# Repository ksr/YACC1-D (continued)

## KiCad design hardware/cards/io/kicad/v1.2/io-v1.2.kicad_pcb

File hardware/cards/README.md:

# hardware/cards

One folder per card: README.md, kicad/ (current), eagle/<rev>/ (deprecated), docs/, bom/.

_Contents migrated 2026-09-19; MIGRATION.md at the repo root says which copy each item came from._

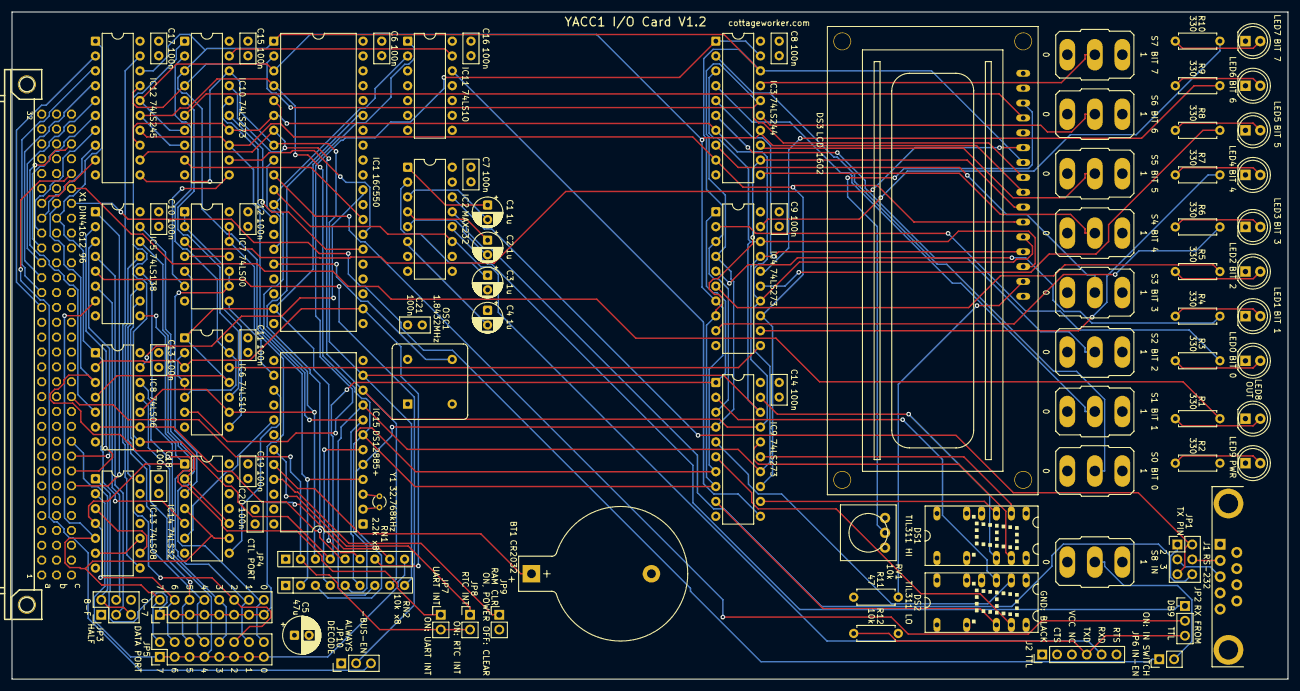
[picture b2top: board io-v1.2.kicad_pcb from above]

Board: 4 copper layers, 218.0 x 114.0 mm, 89 parts (0 on the bottom side), 129 nets.

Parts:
BT1: CR2032; BatteryHolder_Keystone_103_1x20mm
C1, C2, C3, C4: 1u; CP_Radial_D5.0mm_P2.50mm
C5: 47u 16V; CP_Radial_D6.3mm_P2.50mm
C6, C7, C8, C9, C10, C11, C12, C13, C14, C15, C16, C17, C18, C19, C20, C21: 100n; C_Disc_D5.0mm_W2.5mm_P2.50mm
DS1: TIL311 HI; HTIL311A
DS2: TIL311 LO; HTIL311A
DS3: LCD 1602; LCD1602
IC1: 16C550; DIP-40_W15.24mm
IC2: MAX232; DIP-16_W7.62mm
IC3: 74LS244; DIP-20_W7.62mm
IC4, IC9, IC10: 74LS273; DIP-20_W7.62mm
IC5: 74LS138; DIP-16_W7.62mm
IC6, IC11: 74LS10; DIP-14_W7.62mm
IC7: 74LS00; DIP-14_W7.62mm
IC8: 74LS06; DIP-14_W7.62mm
IC12: 74LS245; DIP-20_W7.62mm
IC13: 74LS08; DIP-14_W7.62mm
IC14: 74LS32; DIP-14_W7.62mm
IC15: DS12885+; DIP-24_W15.24mm
J1: RS-232; DSUB-9_Socket_Horizontal_IO-V1.1
J2: TTL SERIAL; PinHeader_1x06_P2.54mm_Vertical
JP1: TX PIN; PinHeader_2x03_P2.54mm_Vertical
JP2: RX FROM; PinHeader_1x03_P2.54mm_Vertical
JP3: HALF; PinHeader_2x03_P2.54mm_Vertical
JP4: CTL PORT; PinHeader_2x08_P2.54mm_Vertical
JP5: DATA PORT; PinHeader_2x08_P2.54mm_Vertical
JP6: IN-EN; PinHeader_1x02_P2.54mm_Vertical
JP7: UART INT; PinHeader_1x02_P2.54mm_Vertical
JP8: RTC INT; PinHeader_1x02_P2.54mm_Vertical
JP9: RAM CLR; PinHeader_1x02_P2.54mm_Vertical
JP10: DECODE; PinHeader_1x03_P2.54mm_Vertical
LED0: 0; LED_D5.0mm
LED1: 1; LED_D5.0mm
LED2: 2; LED_D5.0mm
LED3: 3; LED_D5.0mm
LED4: 4; LED_D5.0mm
LED5: 5; LED_D5.0mm
LED6: 6; LED_D5.0mm
LED7: 7; LED_D5.0mm
LED8: OUT; LED_D5.0mm
LED9: PWR; LED_D5.0mm
OSC1: 1.8432MHz; Oscillator_DIP-8
R1, R2, R3, R4, R5, R6, R7, R8, R9, R10: 330; R_Axial_DIN0207_L6.3mm_D2.5mm_P7.62mm_Horizontal
R11: 47; R_Axial_DIN0207_L6.3mm_D2.5mm_P7.62mm_Horizontal
R12: 10k; R_Axial_DIN0207_L6.3mm_D2.5mm_P7.62mm_Horizontal
RN1: 2.2k x8; R_Array_SIP9
RN2: 10k x8; R_Array_SIP9
RV1: 10k; Potentiometer_Trim_3386_Inline
S0: 0; SW_Toggle_M9040P
S1: 1; SW_Toggle_M9040P
S2: 2; SW_Toggle_M9040P
S3: 3; SW_Toggle_M9040P
S4: 4; SW_Toggle_M9040P
S5: 5; SW_Toggle_M9040P
S6: 6; SW_Toggle_M9040P
S7: 7; SW_Toggle_M9040P
S8: IN; SW_Toggle_M9040P
X1: DIN41612 96; FABC96R
Y1: 32.768kHz; Crystal_C26-LF_D2.1mm_L6.5mm_Vertical

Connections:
/-B-RESET: IC4.1, IC8.8, IC9.1, IC10.1, RN1.4
/-BUS-EN: JP10.3, X1.C28
/-INT: JP7.2, JP8.2, RN1.2, X1.C13
/-IO-ADDRSEL: IC7.12, IC7.13, IC13.1, JP4.1, JP4.3, JP4.5, JP4.7, JP4.9, JP4.11, JP4.13, JP4.15, RN1.8
/-IO-DATASEL: IC8.11, IC13.2, JP5.1, JP5.3, JP5.5, JP5.7, JP5.9, JP5.11, JP5.13, JP5.15, RN1.9
/-IO-RD: IC8.1, IC12.1, IC14.5, X1.B25
/-IO-SEL0: IC5.15, JP4.16, JP5.16
/-IO-SEL1: IC5.14, JP4.14, JP5.14
/-IO-SEL2: IC5.13, JP4.12, JP5.12
/-IO-SEL3: IC5.12, JP4.10, JP5.10
/-IO-SEL4: IC5.11, JP4.8, JP5.8
/-IO-SEL5: IC5.10, JP4.6, JP5.6
/-IO-SEL6: IC5.9, IC13.4, IC14.1, JP4.4, JP5.4
/-IO-SEL7: IC5.7, IC13.5, IC14.4, IC14.9, JP4.2, JP5.2
/-IO-WR: IC8.3, IC14.2, IC14.10, X1.B26
/-RESET: IC8.5, X1.C30
/AS#: IC7.9, IC7.10, IC14.3
/BUFEN#: IC12.19, IC13.8
/C1+: C1.1, IC2.1
/C1-: C1.2, IC2.3
/C2+: C2.1, IC2.4
/C2-: C2.2, IC2.5
/CTLCK: IC7.6, IC10.11
/DATA0: IC12.2, X1.A19
/DATA1: IC12.3, X1.A20
/DATA2: IC12.4, X1.A21
/DATA3: IC12.5, X1.A22
/DATA4: IC12.6, X1.A23
/DATA5: IC12.7, X1.A24
/DATA6: IC12.8, X1.A25
/DATA7: IC12.9, X1.A26
/DB9-2: J1.2, JP1.4
/DB9-3: J1.3, JP1.3
/G2B#: IC5.5, JP10.2
/HALF-G1: IC5.6, JP3.4
/HALF-G2A: IC5.4, JP3.3
/ICLK: IC1.9, IC1.15
/ID0: DS3.7, IC1.1, IC3.18, IC4.3, IC9.3, IC10.3, IC12.18, IC15.4, RN2.2
/ID1: DS3.8, IC1.2, IC3.16, IC4.4, IC9.4, IC10.4, IC12.17, IC15.5, RN2.3
/ID2: DS3.9, IC1.3, IC3.14, IC4.7, IC9.7, IC10.7, IC12.16, IC15.6, RN2.4
/ID3: DS3.10, IC1.4, IC3.12, IC4.8, IC9.8, IC10.8, IC12.15, IC15.7, RN2.5
/ID4: DS3.11, IC1.5, IC3.9, IC4.13, IC9.13, IC10.13, IC12.14, IC15.8, RN2.6
/ID5: DS3.12, IC1.6, IC3.7, IC4.14, IC9.14, IC10.14, IC12.13, IC15.9, RN2.7
/ID6: DS3.13, IC1.7, IC3.5, IC4.17, IC9.17, IC10.17, IC12.12, IC15.10, RN2.8
/ID7: DS3.14, IC1.8, IC3.3, IC4.18, IC9.18, IC10.18, IC12.11, IC15.11, RN2.9
/IN: JP6.1, X1.C26
/INSW: JP6.2, S8.2
/IO-ADDR0: IC5.1, X1.C7
/IO-ADDR1: IC5.2, X1.C8
/IO-ADDR2: IC5.3, X1.C9
/IO-ADDR3: JP3.2, JP3.5, X1.C10
/IO-ADDRSEL: IC7.4, IC7.11
/IO-RD: IC1.22, IC6.3, IC8.2, RN1.7
/IO-SELDATA: IC1.12, IC6.2, IC6.4, IC6.9, IC8.10, IC11.2, RN1.3
/IO-WR: IC1.19, IC6.1, IC6.11, IC7.5, IC8.4, IC11.1, RN1.6
/LCD-BL: DS3.15, R11.2
/LCD-E: DS3.6, IC7.3
/LCD-ENABLE: IC6.10, IC10.5
/LCD-REGISTER: DS3.4, IC10.6
/LCD-VO: DS3.3, RV1.2
/LCDSTB#: IC6.8, IC7.1, IC7.2
/LEDA0: LED0.2, R3.1
/LEDA1: LED1.2, R4.1
/LEDA2: LED2.2, R5.1
/LEDA3: LED3.2, R6.1
/LEDA4: LED4.2, R7.1
/LEDA5: LED5.2, R8.1
/LEDA6: LED6.2, R9.1
/LEDA7: LED7.2, R10.1
/LEDCK: IC4.11, IC6.12
/LQ0: IC4.2, R3.2
/LQ1: IC4.5, R4.2
/LQ2: IC4.6, R5.2
/LQ3: IC4.9, R6.2
/LQ4: IC4.12, R7.2
/LQ5: IC4.15, R8.2
/LQ6: IC4.16, R9.2
/LQ7: IC4.19, R10.2
/OUT: R1.2, X1.C27
/OUTA: LED8.2, R1.1
/PWRA: LED9.2, R2.1
/RCLR#: IC15.21, JP9.1
/RESET: IC1.35, IC8.6, IC8.9, RN1.5
/RTC-AS: IC7.8, IC15.14
/RTC-IRQ#: IC15.19, JP8.1
/RTC-RD#: IC14.6, IC15.17
/RTC-WR#: IC14.8, IC15.15
/RTC-X1: IC15.2, Y1.1
/RTC-X2: IC15.3, Y1.2
/RX: IC1.10, JP2.2
/RX-232: IC2.12, JP2.1
/RX-IN: IC2.13, JP1.1, JP1.6
/RX-TTL: J2.4, JP2.3, R12.1
/SELPORT#: IC13.3, IC13.9
/SELRTC#: IC13.6, IC13.10
/SW0: IC3.2, S0.2
/SW1: IC3.4, S1.2
/SW2: IC3.6, S2.2
/SW3: IC3.8, S3.2
/SW4: IC3.11, S4.2
/SW5: IC3.13, S5.2
/SW6: IC3.15, S6.2
/SW7: IC3.17, S7.2
/SWITCH-LED: IC6.5, IC6.13, IC10.2
/SWOE#: IC3.1, IC3.19, IC6.6
/TH0: DS1.3, IC9.12
/TH1: DS1.2, IC9.15
/TH2: DS1.13, IC9.16
/TH3: DS1.12, IC9.19
/TIL311: IC10.19, IC11.13
/TILCK: IC9.11, IC11.12
/TL0: DS2.3, IC9.2
/TL1: DS2.2, IC9.5
/TL2: DS2.13, IC9.6
/TL3: DS2.12, IC9.9
/TX: IC1.11, IC2.11, J2.5
/TX-OUT: IC2.14, JP1.2, JP1.5
/UART-A0: IC1.28, IC10.9
/UART-A1: IC1.27, IC10.12
/UART-A2: IC1.26, IC10.15
/UART-CS: IC1.13, IC10.16
/UART-INT: IC1.30, IC8.13
/UCLK: IC1.16, OSC1.5
/UINT#: IC8.12, JP7.1
/V+: C3.1, IC2.2
/V-: C4.2, IC2.6
/VBAT: BT1.1, IC15.20
GND: BT1.2, C4.1, C5.2, C6.2, C7.2, C8.2, C9.2, C10.2, C11.2, C12.2, C13.2, C14.2, C15.2, C16.2, C17.2, C18.2, C19.2, C20.2, C21.2, DS1.5, DS1.7, DS1.8, DS2.5, DS2.7, DS2.8, DS3.1, DS3.5, DS3.16, IC1.14, IC1.20, IC1.25, IC2.8, IC2.15, IC3.10, IC4.10, IC5.8, IC6.7, IC7.7, IC8.7, IC9.10, IC10.10, IC11.3, IC11.4, IC11.5, IC11.7, IC11.9, IC11.10, IC11.11, IC12.10, IC13.7, IC13.12, IC13.13, IC14.7, IC14.12, IC14.13, IC15.1, IC15.12, IC15.13, IC15.16, J1.5, J1.SH, J2.1, J2.2, JP3.1, JP9.2, JP10.1, LED0.1, LED1.1, LED2.1, LED3.1, LED4.1, LED5.1, LED6.1, LED7.1, LED8.1, LED9.1, OSC1.4, RV1.3, S0.3, S1.3, S2.3, S3.3, S4.3, S5.3, S6.3, S7.3, S8.3, X1.A1, X1.A32, X1.B1, X1.B32, X1.C1, X1.C32
VCC: C3.2, C5.1, C6.1, C7.1, C8.1, C9.1, C10.1, C11.1, C12.1, C13.1, C14.1, C15.1, C16.1, C17.1, C18.1, C19.1, C20.1, C21.1, DS1.1, DS1.14, DS2.1, DS2.14, DS3.2, IC1.18, IC1.21, IC1.36, IC1.37, IC1.38, IC1.39, IC1.40, IC2.10, IC2.16, IC3.20, IC4.20, IC5.16, IC6.14, IC7.14, IC8.14, IC9.20, IC10.20, IC11.14, IC12.20, IC13.14, IC14.14, IC15.18, IC15.24, JP3.6, OSC1.1, OSC1.8, R2.2, R11.1, R12.2, RN1.1, RN2.1, RV1.1, S0.1, S1.1, S2.1, S3.1, S4.1, S5.1, S6.1, S7.1, S8.1, X1.A2, X1.A31, X1.B2, X1.B31, X1.C2, X1.C31

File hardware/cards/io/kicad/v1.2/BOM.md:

# I/O card V1.2 - bill of materials

GENERATED by `gen_io12.py bom` from `io12_netlist.py` (2026-11-18) - do not edit. 89 parts. Buy every IC in a socket (the UART, the clock chip and the TIL311s at least): 6 x 14-pin 7.62 mm, 2 x 16-pin 7.62 mm, 5 x 20-pin 7.62 mm, 1 x 24-pin 15.24 mm, 1 x 40-pin 15.24 mm; a 4-pin socket for the oscillator, two 14-pin sockets for the TIL311s and a 16-way socket strip for the LCD.

| Qty | Value | Footprint | References | Buy / note |
|---|---|---|---|---|
| 1 | CR2032 | BatteryHolder_Keystone_103_1x20mm | BT1 | Keystone 103, a flat holder for one CR2032 (an upright holder is taller than the room between cards) |
| 4 | 1u | CP_Radial_D5.0mm_P2.50mm | C1, C2, C3, C4 |  |
| 1 | 47u 16V | CP_Radial_D6.3mm_P2.50mm | C5 | bulk |
| 16 | 100n | C_Disc_D5.0mm_W2.5mm_P2.50mm | C6, C7, C8, C9, C10, C11, C12, C13, C14, C15, C16, C17, C18, C19, C20, C21 |  |
| 1 | TIL311 HI | HTIL311A | DS1 | TIL311 (or HP 5082-7340: same pins), in a socket |
| 1 | TIL311 LO | HTIL311A | DS2 | TIL311 (or HP 5082-7340), in a socket |
| 1 | LCD 1602 | LCD1602 | DS3 | HD44780 16 x 2 module, 80 x 36 mm, a 16-pin row along its upper edge (pin 1 at the left), on a 16-way socket strip and four 2.5 mm standoffs |
| 1 | 16C550 | DIP-40_W15.24mm | IC1 | a 16550 in DIP-40: Exar XR16C550CP (the V1.1 card's), TI TL16C550CN or PC16550DN |
| 1 | MAX232 | DIP-16_W7.62mm | IC2 | MAX232 with 1 uF capacitors (a MAX232A or MAX202 runs on them too) |
| 1 | 74LS244 | DIP-20_W7.62mm | IC3 | switch buffer: S0-S7 to ID0-7 (IN P1 with SWITCH-LED) |
| 3 | 74LS273 | DIP-20_W7.62mm | IC4, IC9, IC10 |  |
| 1 | 74LS138 | DIP-16_W7.62mm | IC5 | port decode: -IO-SEL0..7, the eight ports of the card's half (JP3) |
| 2 | 74LS10 | DIP-14_W7.62mm | IC6, IC11 |  |
| 1 | 74LS00 | DIP-14_W7.62mm | IC7 | the LCD's E; the control latch's clock; the clock chip's AS; IO-ADDRSEL |
| 1 | 74LS06 | DIP-14_W7.62mm | IC8 | open collector: IO-RD, IO-WR, RESET, -B-RESET, IO-SELDATA, the UART's -INT |
| 1 | 74LS245 | DIP-20_W7.62mm | IC12 | data buffer: the bus's DATA0-7 to the card's ID0-7, direction from -IO-RD |
| 1 | 74LS08 | DIP-14_W7.62mm | IC13 | the buffer's enable: one of the card's four ports addressed; one gate spare |
| 1 | 74LS32 | DIP-14_W7.62mm | IC14 | the clock chip's strobes from the bus's -IO-RD and -IO-WR; one gate spare |
| 1 | DS12885+ | DIP-24_W15.24mm | IC15 | DS12885+ (Analog Devices / Maxim), the 24-pin PDIP: not the DS12887 module (its pins 2, 3, 20 are not connected) |
| 1 | RS-232 | DSUB-9_Socket_Horizontal_IO-V1.1 | J1 | 9-way D socket (female), right angle, as the V1.1 card's: pin rows 2.84 mm apart, 10.2 mm behind the board's edge, mounting holes 25.0 mm apart |
| 1 | TTL SERIAL | PinHeader_1x06_P2.54mm_Vertical | J2 | 6-pin header, 2.54 mm: an FTDI TTL-232R-5V cable's socket, its black wire (GND) on pin 1 |
| 1 | TX PIN | PinHeader_2x03_P2.54mm_Vertical | JP1 | the null-modem block. 1-3 and 2-4: the card sends on DB9 pin 2; 3-5 and 4-6: on pin 3 |
| 1 | RX FROM | PinHeader_1x03_P2.54mm_Vertical | JP2 | 1-2: the UART hears the DB9; 2-3: the TTL header |
| 1 | HALF | PinHeader_2x03_P2.54mm_Vertical | JP3 | 3-5 and 4-6: ports P0-P7; 1-3 and 2-4: P8-PF |
| 1 | CTL PORT | PinHeader_2x08_P2.54mm_Vertical | JP4 | one jumper: the control port. 15-16 = port 0 ... 1-2 = port 7 |
| 1 | DATA PORT | PinHeader_2x08_P2.54mm_Vertical | JP5 | one jumper: the data port. 13-14 = port 1 |
| 1 | IN-EN | PinHeader_1x02_P2.54mm_Vertical | JP6 | fitted: the IN switch drives the bus line IN |
| 1 | UART INT | PinHeader_1x02_P2.54mm_Vertical | JP7 | fitted: the UART's INT drives -INT |
| 1 | RTC INT | PinHeader_1x02_P2.54mm_Vertical | JP8 | fitted: the clock's -IRQ drives -INT |
| 1 | RAM CLR | PinHeader_1x02_P2.54mm_Vertical | JP9 | fitted with the power off: the clock chip's RAM is cleared |
| 1 | DECODE | PinHeader_1x03_P2.54mm_Vertical | JP10 | 1-2: the ports are decoded always, as on V1.1 (the bus tester can drive the card); 2-3: only while -BUS-EN is low |
| 1 | 0 | LED_D5.0mm | LED0 | LED bit 0 |
| 1 | 1 | LED_D5.0mm | LED1 | LED bit 1 |
| 1 | 2 | LED_D5.0mm | LED2 | LED bit 2 |
| 1 | 3 | LED_D5.0mm | LED3 | LED bit 3 |
| 1 | 4 | LED_D5.0mm | LED4 | LED bit 4 |
| 1 | 5 | LED_D5.0mm | LED5 | LED bit 5 |
| 1 | 6 | LED_D5.0mm | LED6 | LED bit 6 |
| 1 | 7 | LED_D5.0mm | LED7 | LED bit 7 |
| 1 | OUT | LED_D5.0mm | LED8 | the bus line OUT (ON / OFF) |
| 1 | PWR | LED_D5.0mm | LED9 | 5 mm LED |
| 1 | 1.8432MHz | Oscillator_DIP-8 | OSC1 | 1.8432 MHz oscillator, 5 V, half-size (8-pin DIP) can, as the V1.1 card's (ECS-2100AX): the monitor's divisor 3 gives 38400 baud. Its pin 1 is tied to +5 V on the board: not connected in the can, or an enable that is on when high |
| 10 | 330 | R_Axial_DIN0207_L6.3mm_D2.5mm_P7.62mm_Horizontal | R1, R2, R3, R4, R5, R6, R7, R8, R9, R10 |  |
| 1 | 47 | R_Axial_DIN0207_L6.3mm_D2.5mm_P7.62mm_Horizontal | R11 | 47 ohm for a module with no resistor of its own for its backlight; a wire link if the module has one |
| 1 | 10k | R_Axial_DIN0207_L6.3mm_D2.5mm_P7.62mm_Horizontal | R12 | the TTL header's line into the UART held high with no cable |
| 1 | 2.2k x8 | R_Array_SIP9 | RN1 | pull-ups: the open-collector strobes, -INT, the two port selects |
| 1 | 10k x8 | R_Array_SIP9 | RN2 | ID0-7 pull-ups (the buffer off) |
| 1 | 10k | Potentiometer_Trim_3386_Inline | RV1 | 10k trimmer, Bourns 3386 with its three pins in a row |
| 1 | 0 | SW_Toggle_M9040P | S0 | M9040P toggle (on-on, PCB pins), as the V1.1 card's |
| 1 | 1 | SW_Toggle_M9040P | S1 | M9040P toggle (on-on, PCB pins), as the V1.1 card's |
| 1 | 2 | SW_Toggle_M9040P | S2 | M9040P toggle (on-on, PCB pins), as the V1.1 card's |
| 1 | 3 | SW_Toggle_M9040P | S3 | M9040P toggle (on-on, PCB pins), as the V1.1 card's |
| 1 | 4 | SW_Toggle_M9040P | S4 | M9040P toggle (on-on, PCB pins), as the V1.1 card's |
| 1 | 5 | SW_Toggle_M9040P | S5 | M9040P toggle (on-on, PCB pins), as the V1.1 card's |
| 1 | 6 | SW_Toggle_M9040P | S6 | M9040P toggle (on-on, PCB pins), as the V1.1 card's |
| 1 | 7 | SW_Toggle_M9040P | S7 | M9040P toggle (on-on, PCB pins), as the V1.1 card's |
| 1 | IN | SW_Toggle_M9040P | S8 | M9040P toggle (on-on, PCB pins), as the V1.1 card's |
| 1 | DIN41612 96 | FABC96R | X1 | bus connector (blank V3.2 card) |
| 1 | 32.768kHz | Crystal_C26-LF_D2.1mm_L6.5mm_Vertical | Y1 | 32.768 kHz watch crystal for a 6 pF load (the DS12885 has the load capacitors inside): a 12.5 pF crystal runs fast |

Shunts: one each for JP4 and JP5 (the two ports), JP2 and JP10 (on 1-2, as V1.1, unless the decoder is to follow -BUS-EN), two each for JP3 and JP1, one for JP6 (IN); JP7, JP8 and JP9 are left open.

The 74LS types are the V1.1 card's. The three latches may be 74HCT273 (the LEDs are a little brighter); the buffer IC12 stays a 74LS245 or 74HCT245 (TTL input levels on both sides).

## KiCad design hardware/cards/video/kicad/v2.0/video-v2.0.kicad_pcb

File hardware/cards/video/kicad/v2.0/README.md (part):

# video-v2.0 — KiCad design master for the video card

**This card will not be built (decided 2026-11-17): the video card to build is the V4 (`../v4.0`,
`docs/cards/video-v4.md`). Nothing here was ordered. The design is kept as it stood, unchanged, for reference; do
not order from this folder.**

**The master since 2026-10-22. Ready to order since 2026-10-23 (re-reviewed, every re-review finding applied); not
ordered. Revised 2026-10-26 before the order: the DB9's VSYNC polarity jumper JP4** (below), the board routed again
2026-10-27, with the board-layout rules' silkscreen and cottageworker.com on it; the gerbers exported again
2026-11-03 with every part's value on the silk (silk only) and, the same day, with each power plane in one piece
(16 power pads connected solid, inner layers only: "Planes (2026-11-03)"; `video-v2.0-gerbers.zip`, what to upload:
"Ordering" below). V2.0 is the v1.3 card (`../v1.3/`: 6845, IDT7134 text RAM,
the DOTS jumper, 12 MHz, both fonts in one character generator) plus a **graphics layer**, **every register on I/O ports
PA-PE** and **two PS/2 ports** on an ATmega328P with an **INT jumper**. The design note is `BACKLOG.md` "Video card
V2.0"; the theory `docs/cards/video-v2.md`; the ATmega's firmware `embedded/video-ps2`; the picture and the CPU
side `tools/vidsim.py --card v2.0`.

**Revised 2026-10-22 after the design review** (`hardware/cards/video/reviews/v2.0.md`, its status table at the top):
every HIGH and MEDIUM finding is in the circuit or the firmware, and two features were added - **direct mode** (with
GFX-ON = 0 the CPU owns the graphics RAM: a plain SRAM at any clock the machine runs) and the **text-only build** (the
graphics chips left off, a status bit saying so). **Re-reviewed 2026-10-23** (`hardware/cards/video/reviews/v2.0-r2.md`,
HIGH 0, MED 1, LOW 9, INFO 6; its status table at the top): the MD-60SM side-leg slots widened (R2-1), IC55's socket
clear of its neighbours (R2-2), the bus -RESET buffered (R2-3), the BOM, the README's statements, the silkscreen, the
timing test and the firmware; the rest are driver rules and bench measurements.

Unlike v1.x (Eagle conversions edited in KiCad) this design is **generated**: `v20_netlist.py` is the circuit,
`gen_v20.py` draws the schematic (since 2026-10-24 a root sheet and eight functional sheets with the nets drawn as
wires: "The schematic" below), builds the board and writes `BOM.md`; `build.sh` routes and checks it. Change the circuit in
`v20_netlist.py`, the placement in `gen_v20.py` (`PLACE`), then run `./build.sh` (KiCad 10, Freerouting 1.9 in `FRJAR`,
default `~/freerouting/freerouting.jar`, which opens a window while it runs; `SEEDS="..."` and `MP=` choose the
component orders and passes). `tools/eagle_to_kicad_all.py` never writes here (`MASTER` marker).

## The board

- **218.42 x 113.97 mm** (x 17.747-236.167): the blank V3.2 card's outline lengthened to the sequencer logic V2.1l's
  218 mm, so it needs the same slot space; X1 (DIN 41612) exactly where every card has it, copper keepouts round its
  two screws.
- **4 layers**, the v1.3 / memory card v2.0 stack-up and rules: In1.Cu a solid GND plane, In2.Cu a solid VCC plane, GND
  and VCC never routed (every power pin is a through-hole pad on its plane); signals 0.25 mm, clearance 0.2 mm, vias
  0.8 / 0.4 mm.
- **Placement** (`gen_v20.py` `PLACE`; pin 1 of every DIP at the top left, each 100 nF beside its IC's VCC pin):
  row A (top) the port decode, strobes, the inverters IC46 (beside the control register they mostly serve), the control
  register, status buffers, the PS/2 and graphics latches, WRQ and the video driver IC27; on the left the 600-mil parts (IC15 text RAM, IC17 6845, IC39 62256, IC25 28C64) and IC18 with SV3 /
  RN2; row B the graphics address muxes, display latch and shifter, the ATmega, with the GD pull-ups RN3 standing between
  IC38 and IC42; under IC42 / IC43, on its side, the direct-mode read buffer IC55 (the band under the muxes is left to
  the routing); row C the text pipeline and the gates, with the text-only pads R25 / R26 in the gaps beside IC1; row D
  the clock chain (IC28, IC21, IC20 with Q2, SV4), the remaining gates (IC32 among them, beside the counter whose QC and
  RCO it ORs) and IC54 (turned round, beside J4); the right
  edge DB9 (X2) with its VSYNC polarity jumper JP4 standing beside it (2026-10-26), RCA (J1), the keyboard (J2) and mouse (J3) Mini-DINs with their faces at the board edge, F1, the FTDI header J4 (a legend
  at every pin), the PWR LED. `gen_v20.py place` checks that no two courtyards overlap and, since the re-review (R2-2),
  that every DIP **socket** fits: each socket's outline (the pin rows + 1.3 mm at the sides, the end pins + 1.9 mm at
  the ends: the widest stamped sockets) clear of every other socket and of every other part's pads and body. The
  closest are IC55 (on its side between IC42 above and IC19 / IC1 below) with 0.02 mm to IC42's and 0.10 to IC19's /
  IC1's, IC55 / C59 0.17, IC49 / R12 0.17, IC25 / IC39 0.18 mm; with turned-pin sockets (1.27 mm end walls) IC55 has
  ~0.65 mm. RN3 and C59 stand 0.3 mm left of the middle of their gap for it.
- **Silkscreen** (R2-9; the board-layout rules since 2026-10-24, below): `gen_v20.py silk` writes every legend afresh
  and places it and every reference clear of the other silk, the pads, the edge and every part's body, its own
  included (`silk_texts()`, `silk_place()`). Each IC's type stands on the reference's line ("IC30 74LS138"); the
  jumpers and the LED carry their function and the jumpers each position's meaning. The jack legends "KEYBOARD (PURPLE)" and
  "MOUSE (GREEN)" stand turned beside each jack's body; the Mini-DIN outline is broken round its side-leg pads and stops
  short of the board edge. The card's name stands in the band under the graphics muxes. Since 2026-11-03 every
  resistor, network, capacitor, crystal and the fuse carries its value beside its reference ("R10 1k", "RN3 10k x8",
  "C16 47u", "Y1 16MHz", "F1 0.5A").

## The board-layout rules (2026-10-24)

The rules for every YACC1 board (switches, buttons, LEDs and outside-cable connectors on the front edge, the edge
farthest from the bus connector; every reference readable with the parts fitted, never under a chip, socket or module,
an IC's type beside it; every switch, button and LED labelled with its function, each position of a switch with what
it selects) came after this board was routed and before it was ordered. V2.0 took them on the **silkscreen only**
(2026-10-24): no part moved, the copper and the drills stayed the route of 2026-10-23 (`ed7c060`, order 5, 285 vias).
The VSYNC jumper JP4 (2026-10-26) follows them too: a jumper block near the front edge, its positions labelled. The
board was routed afresh for it ("Results"). Every part's value beside its reference (2026-11-03) came the same way,
on the silkscreen only ("Part values" below).

| Rule | On this board |
|---|---|
| front edge | the DB9 X2, the RCA J1, the PS/2 jacks J2 / J3 and the PWR LED stand at the right-hand edge, opposite X1; the DB9's VSYNC jumper JP4 stands beside the DB9. The FTDI header J4 (the ATmega's programming port) stays where it is, 24 mm in from that edge, with its pin legend: moving it would mean a new route |
| IC type beside the reference | all 40 ICs, on one line with the reference ("IC30 74LS138"): the value of each as the parts list has it, the grade included - IC17 **HD68B45SP / MC68B45P**, IC25 **AT28C64B-15**, IC49 **ATmega328P-P** (2026-11-10; "6845", "28C64" and "ATmega328P" before). Above the IC where there is room, else below it, else turned in the gap beside it (IC19, IC28, IC49 on the left, IC53 on the right); IC49's, too long for its gap on one line, stands there on two ("Labels" below) |
| no reference under a part | every text is kept off every part's body, its own included (its ink off the bodies below, and since 2026-11-10 its whole text box off every part's Fab outline, as `pcb-check` measures it): a DIP's body is the outline of the widest stamped socket (`socket_check`: the pin rows + 1.3 mm, the end pins + 1.9 mm), X1's the DIN 41612 housing (its silk, pads and 2.5 mm past its ends), J1's its outline and pads. R10, R25, R26 and R27 had their references inside their own outline: they now stand beside it. X1's reference left the housing's end (at the top-left corner, x 18.9, y 16.1, until 2026-11-10; now beside the housing with its type, "X1 DIN41612 96"); J1's, hidden by the RCA library footprint, is shown left of the jack. Checked by the texts' ink against every body and socket outline: before, 37 references stood on one - 26 capacitors' on a neighbouring IC's socket wall, IC1's on IC55's socket, IC19's, IC25's and IC54's on their own socket, J2's on J1, R15's and RN3's on IC25's / IC38's socket, R10's, R25's, R26's and R27's on their own body; now none |
| functions and positions | **LED1 PWR**. **JP2 DOTS**, "ON=8 OFF=6" (fitted: 8 dots a character, 64 x 24 with graphics; open: 6 dots, 80 x 24). **JP3 INT-EN**, "ON: PS/2 -INT" / "OFF: NO -INT" (fitted: IC27/D's open collector drives the bus -INT; open: the card never touches -INT). **SV3 BLOCK**, "A15" .. "A12" beside the pairs 1-2 .. 7-8 and "ON=0" (each pair sets the address bit the board select IC18 compares, fitted = 0, open = 1 through RN2; $D000 = 5-6 only). **SV4 DOTCLK**, "XTAL" over pin 1 and "XTAL/2" over pin 3 (1-2: DOTCLOCK the crystal; 2-3: half of it). **JP4 VSYNC**, "+VS CGA" beside pin 1 and "-VS MDA" beside pin 3 (1-2: DB9 pin 9 positive VSYNC, a TV-rate or CGA monitor; 2-3: negative, an MDA monitor; 2026-10-26). The meanings are those of `v20_netlist.py` and `docs/cards/video.md` (sections 3.1, 3.4) and `docs/cards/video-v2.md` |
| part values (2026-11-03) | all 69 resistors, networks, capacitors, crystals and the fuse: the value beside the reference, from `v20_netlist.py` (C16 **47u** for 47u 16V, F1 **0.5A** for 0.5A PTC). 63 on one line or stacked with the reference beside the part; C34 and C38 with the reference beside the part and the value next to it; C3 and C20 with the reference beside the part and the value in the legend "C3 C20: 100n" right of IC55 (no room beside them); C27 and C58 as one block beside their part's neighbour (below) |
| text size | every reference and legend 1.0 mm high with 0.15 mm strokes, JLCPCB's standard legend (the card's name 1.5 mm); "DOTS", "INT-EN" and "TEXT-ONLY" were 0.8 mm. X1's library pin numbers "1" and "32" stay 0.8 mm (0.15 mm strokes; at 1.0 mm "32" meets the housing's outline), JLCPCB's high-precision legend size |

`gen_v20.py silk` places the texts by their ink (not KiCad's taller text box), 0.15 mm from other silk (1.0 mm after an
IC's label), 0.2 mm from pads, 0.4 mm from the edge; an IC's label goes above it, else below, else turned in the gap at
its right, then its left, along that side and within its length. A second run leaves every text where it is.

**Part values (2026-11-03).** The rule for every new card (every part's type or value beside its reference, never
under a fitted part) reached V2.0 as a silkscreen change only, like the rules of 2026-10-24: no part moved, copper and
drills as routed 2026-10-27. Each resistor's, network's, capacitor's, crystal's and the fuse's value is its
`COMPANION` text, placed with the reference by `silk_place()` in this order: on one line or stacked, beside the part
(along one of its sides, within its length); else the reference beside the part and the value beside it too, nearest
the reference; else the value next to the reference wherever that is clear; else the reference beside the part and
the value in a legend with the others' that found no room ("C3 C20: 100n"); else the block at the nearest clear place.
A passive's reference and a value standing apart from it must be nearer their own part than any other non-IC part, so
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
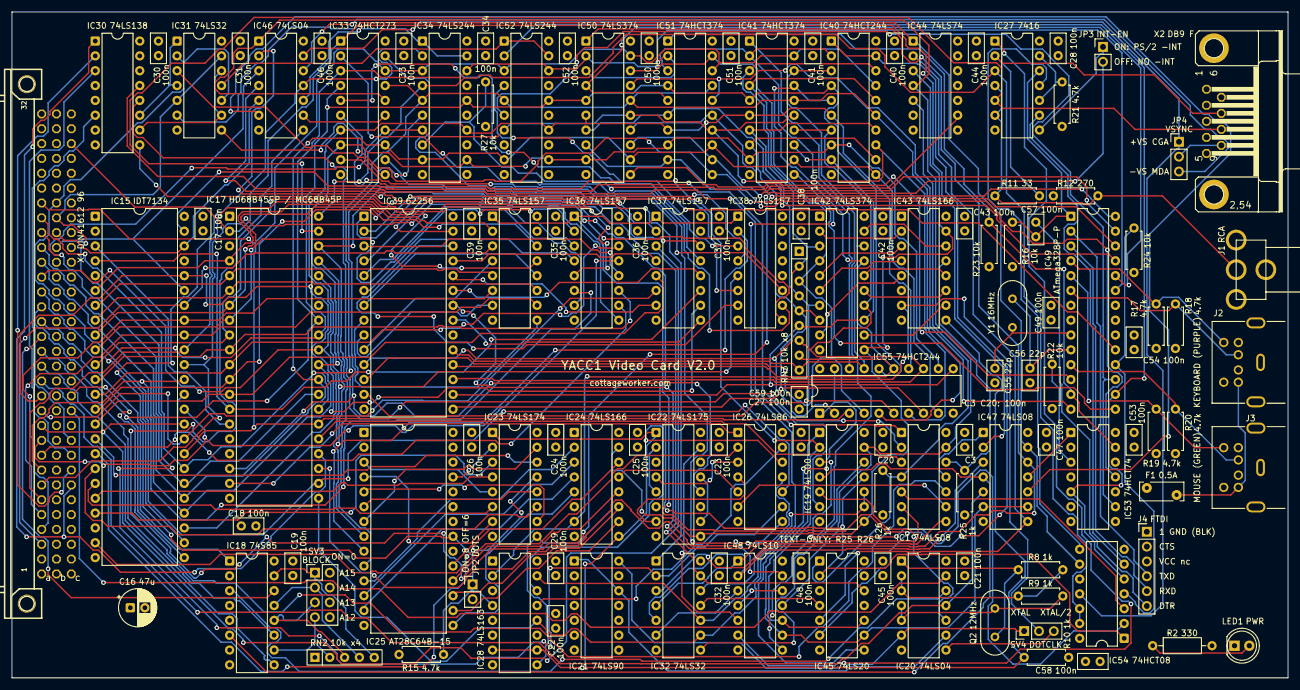
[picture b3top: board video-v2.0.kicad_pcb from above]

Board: 4 copper layers, 218.4 x 114.0 mm, 121 parts (0 on the bottom side), 219 nets.

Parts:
C3, C17, C18, C19, C20, C21, C22, C23, C24, C25, C26, C27, C28, C29, C30, C31, C32, C33, C34, C35, C36, C37, C38, C39, C40, C41, C42, C43, C44, C45, C46, C47, C48, C49, C50, C51, C52, C53, C54, C57, C58, C59: 100n; C_Disc_D5.0mm_W2.5mm_P2.50mm
C16: 47u 16V; CP_Radial_D6.3mm_P2.50mm
C55, C56: 22p; C_Disc_D5.0mm_W2.5mm_P2.50mm
F1: 0.5A PTC; Fuse_Bourns_MF-RHT050
IC1: 74ALS08; DIP-14_W7.62mm
IC15: IDT7134; DIP-48_W15.24mm
IC17: HD68B45SP / MC68B45P; DIP-40_W15.24mm
IC18: 74S85; DIP-16_W7.62mm
IC19: 74LS00; DIP-14_W7.62mm
IC20, IC46: 74LS04; DIP-14_W7.62mm
IC21: 74LS90; DIP-14_W7.62mm
IC22: 74LS175; DIP-16_W7.62mm
IC23: 74LS174; DIP-16_W7.62mm
IC24, IC43: 74LS166; DIP-16_W7.62mm
IC25: AT28C64B-15; DIP-28_W15.24mm
IC26: 74LS86; DIP-14_W7.62mm
IC27: 7416; DIP-14_W7.62mm
IC28: 74LS163; DIP-16_W7.62mm
IC30: 74LS138; DIP-16_W7.62mm
IC31, IC32: 74LS32; DIP-14_W7.62mm
IC33: 74HCT273; DIP-20_W7.62mm
IC34, IC52: 74LS244; DIP-20_W7.62mm
IC35, IC36, IC37, IC38: 74LS157; DIP-16_W7.62mm
IC39: 62256; DIP-28_W15.24mm
IC40, IC55: 74HCT244; DIP-20_W7.62mm
IC41, IC51: 74HCT374; DIP-20_W7.62mm
IC42, IC50: 74LS374; DIP-20_W7.62mm
IC44: 74LS74; DIP-14_W7.62mm
IC45: 74LS20; DIP-14_W7.62mm
IC47: 74LS08; DIP-14_W7.62mm
IC48: 74LS10; DIP-14_W7.62mm
IC49: ATmega328P-P; DIP-28_W7.62mm
IC53: 74HCT74; DIP-14_W7.62mm
IC54: 74HCT08; DIP-14_W7.62mm
J1: RCA
J2: KEYBOARD; MiniDIN6_MD-60SM
J3: MOUSE; MiniDIN6_MD-60SM
J4: FTDI; PinHeader_1x06_P2.54mm_Vertical
JP2: DOTS 8=ON; PinHeader_1x02_P2.54mm_Vertical
JP3: INT-EN; PinHeader_1x02_P2.54mm_Vertical
JP4: VSYNC +/-; PinHeader_1x03_P2.54mm_Vertical
LED1: PWR; LED_D5.0mm
Q2: 12MHz; Crystal_HC49-U_Vertical
R2: 330; R_Axial_DIN0207_L6.3mm_D2.5mm_P10.16mm_Horizontal
R8, R9, R10, R25, R26: 1k; R_Axial_DIN0207_L6.3mm_D2.5mm_P7.62mm_Horizontal
R11: 33; R_Axial_DIN0207_L6.3mm_D2.5mm_P7.62mm_Horizontal
R12: 270; R_Axial_DIN0207_L6.3mm_D2.5mm_P7.62mm_Horizontal
R15, R17, R18, R19, R20, R21: 4.7k; R_Axial_DIN0207_L6.3mm_D2.5mm_P7.62mm_Horizontal
R16, R22, R23, R24, R27: 10k; R_Axial_DIN0207_L6.3mm_D2.5mm_P7.62mm_Horizontal
RN2: 10k x4; R_Array_SIP5
RN3: 10k x8; R_Array_SIP9
SV3: BLOCK; PinHeader_2x04_P2.54mm_Vertical
SV4: DOTCLK; PinHeader_1x03_P2.54mm_Vertical
X1: DIN41612 96; FABC96R
X2: DB9 F; F09HP
Y1: 16MHz; Crystal_HC49-U_Vertical

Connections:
/-INT: JP3.2, X1.C13
/-IO-RD: IC26.9, IC31.5, IC31.13, IC32.2, X1.B25
/-IO-WR: IC17.22, IC26.10, IC31.2, IC31.10, X1.B26
/-MEM-RD: IC15.43, IC46.3, X1.B23
/-MEM-WR: IC15.46, IC46.5, X1.B24
/-RESET: IC17.2, IC33.1, IC44.1, IC47.13, IC54.9, X1.C30
/-VMA: IC20.13, X1.C12
/ADDR0: IC15.42, IC35.3, X1.A3
/ADDR1: IC15.41, IC35.6, X1.A4
/ADDR2: IC15.40, IC35.10, X1.A5
/ADDR3: IC15.39, IC35.13, X1.A6
/ADDR4: IC15.38, IC36.3, X1.A7
/ADDR5: IC15.37, IC36.6, X1.A8
/ADDR6: IC15.36, IC36.10, X1.A9
/ADDR7: IC15.35, IC36.13, X1.A10
/ADDR8: IC15.34, IC37.3, X1.A11
/ADDR9: IC15.33, IC37.6, X1.A12
/ADDR10: IC15.44, IC37.10, X1.A13
/ADDR11: IC20.11, IC47.5, X1.A14
/ADDR12: IC18.9, X1.A15
/ADDR13: IC18.11, X1.A16
/ADDR14: IC18.14, X1.A17
/ADDR15: IC18.1, X1.A18
/ATTR1: IC22.4, IC26.3
/ATTR2: IC22.2, IC22.5
/ATTR3: IC22.7, IC26.4
/BOARDSEL: IC18.6, IC19.4, IC47.4
/BUSY: IC49.17, IC52.6, IC53.9
/CA3: IC23.15, IC25.7
/CA4: IC23.12, IC25.6
/CA5: IC23.10, IC25.5
/CA6: IC23.7, IC25.4
/CA7: IC23.5, IC25.3
/CA8: IC23.2, IC25.25
/CG0: IC24.2, IC25.11
/CG1: IC24.3, IC25.12
/CG2: IC24.4, IC25.13
/CG3: IC24.5, IC25.15
/CG4: IC24.10, IC25.16
/CG5: IC24.11, IC25.17
/CG6: IC24.12, IC25.18
/CG7: IC24.14, IC25.19
/CHARCLOCK: IC19.8, IC22.9, IC23.9, IC24.15, IC28.9, IC42.11, IC43.15, IC44.3
/CMDCLK: IC31.8, IC51.11, IC53.11
/CNTEN: IC22.1, IC23.1, IC24.9, IC28.7, IC28.10, IC43.9, R10.1
/CNTQA: IC26.12, IC28.14
/CNTQB: IC26.13, IC28.13
/CPAGE: IC33.9, IC38.10
/CRTCCLOCK: IC17.21, IC28.12, IC32.9, IC41.11
/CRTCCS: IC1.3, IC17.25
/CRTCE: IC17.23, IC26.8
/CTLCLK: IC31.3, IC33.11
/CURSOR: IC17.19, IC26.1
/DATA0: IC15.25, IC17.33, IC33.3, IC34.18, IC40.2, IC41.2, IC50.2, IC51.3, IC52.18, IC55.18, X1.A19
/DATA1: IC15.26, IC17.32, IC33.4, IC34.16, IC40.4, IC41.5, IC50.5, IC51.4, IC52.16, IC55.16, X1.A20
/DATA2: IC15.27, IC17.31, IC33.7, IC34.14, IC40.6, IC41.6, IC50.6, IC51.7, IC52.14, IC55.14, X1.A21
/DATA3: IC15.28, IC17.30, IC33.8, IC34.12, IC40.8, IC41.9, IC50.9, IC51.8, IC52.12, IC55.12, X1.A22
/DATA4: IC15.29, IC17.29, IC33.13, IC34.9, IC40.11, IC41.12, IC50.12, IC51.13, IC52.9, IC55.9, X1.A23
/DATA5: IC15.30, IC17.28, IC33.14, IC34.7, IC40.13, IC41.15, IC50.15, IC51.14, IC52.7, IC55.7, X1.A24
/DATA6: IC15.31, IC17.27, IC33.17, IC34.5, IC40.15, IC41.16, IC50.16, IC51.17, IC52.5, IC55.5, X1.A25
/DATA7: IC15.32, IC17.26, IC33.18, IC34.3, IC40.17, IC41.19, IC50.19, IC51.18, IC52.3, IC55.3, X1.A26
/DB9VS: JP4.2, X2.9
/DE: IC17.18, IC22.12, IC34.6
/DE2: IC22.10, IC22.13
/DE3: IC22.15, IC48.5
/DOTCLKH: IC20.8, SV4.3
/DOTCLOCK: IC24.7, IC28.2, IC43.7, SV4.2
/DOTS: IC25.21, IC28.4, IC34.2, IC46.11, JP2.1, R15.2
/DPAGE: IC33.12, IC38.11
/DRDOE: IC45.8, IC55.1, IC55.19
/EIGHT: IC46.10, IC47.2
/FDTR: C57.1, J4.6
/FRX: IC49.3, J4.5
/FTX: IC49.2, J4.4
/FULL: IC49.16, IC52.2, IC53.5, IC54.5
/FULLCLR: IC47.11, IC53.1
/GA0: IC35.4, IC39.10
/GA1: IC35.7, IC39.9
/GA2: IC35.9, IC39.8
/GA3: IC35.12, IC39.7
/GA4: IC36.4, IC39.6
/GA5: IC36.7, IC39.5
/GA6: IC36.9, IC39.4
/GA7: IC36.12, IC39.3
/GA8: IC37.4, IC39.25
/GA9: IC37.7, IC39.24
/GA10: IC37.9, IC39.21
/GA11: IC37.12, IC39.23
/GA12: IC38.4, IC39.2
/GA13: IC38.7, IC39.26
/GA14: IC38.9, IC39.1
/GD0: IC39.11, IC40.18, IC41.3, IC42.3, IC55.2, RN3.2
/GD1: IC39.12, IC40.16, IC41.4, IC42.4, IC55.4, RN3.3
/GD2: IC39.13, IC40.14, IC41.7, IC42.7, IC55.6, RN3.4
/GD3: IC39.15, IC40.12, IC41.8, IC42.8, IC55.8, RN3.5
/GD4: IC39.16, IC40.9, IC41.13, IC42.13, IC55.11, RN3.6
/GD5: IC39.17, IC40.7, IC41.14, IC42.14, IC55.13, RN3.7
/GD6: IC39.18, IC40.5, IC41.17, IC42.17, IC55.15, RN3.8
/GD7: IC39.19, IC40.3, IC41.18, IC42.18, IC55.17, RN3.9
/GDA: IC1.11, IC47.1
/GDG: IC32.5, IC47.3, IC48.2
/GDOT: IC1.12, IC43.13, R25.1
/GFXON: IC1.13, IC19.13, IC33.16, IC44.4, IC46.1, IC48.11
/GL0: IC42.2, IC43.2
/GL1: IC42.5, IC43.3
/GL2: IC42.6, IC43.4
/GL3: IC42.9, IC43.5
/GL4: IC42.12, IC43.10
/GL5: IC42.15, IC43.11
/GL6: IC42.16, IC43.12
/GL7: IC42.19, IC43.14
/GOR: IC32.6, IC48.3
/GRDOE: IC19.3, IC54.2
/GSEL: IC19.1, IC45.9, IC47.6, IC47.9, IC48.9
/GWE: IC39.27, IC40.1, IC40.19, IC45.6
/GWR: IC44.2, IC45.5, IC47.8
/HSYNC: IC17.39, IC27.5, X2.8
/INTG: IC27.9, IC54.6
/INTOC: IC27.8, JP3.1
/INTREQ: IC49.18, IC54.4, R24.1
/IO-ADDR0: IC17.24, IC30.1, X1.C7
/IO-ADDR1: IC30.2, X1.C8
/IO-ADDR2: IC30.3, X1.C9
/IO-ADDR3: IC30.6, X1.C10
/KCLK: IC49.4, J2.5, R17.1
/KDAT: IC49.6, J2.1, R18.1
/LDDATA: IC49.12, IC50.11, IC53.3, R22.1
/MCLK: IC49.5, J3.5, R19.1
/MD0: IC49.23, IC50.3, IC51.2
/MD1: IC49.24, IC50.4, IC51.5
/MD2: IC49.25, IC50.7, IC51.6
/MD3: IC49.26, IC50.8, IC51.9
/MD4: IC49.27, IC50.13, IC51.12
/MD5: IC49.28, IC50.14, IC51.15
/MD6: IC49.14, IC50.17, IC51.16
/MD7: IC49.15, IC50.18, IC51.19
/MDAT: IC49.11, J3.1, R20.1
/MEMRD: IC19.2, IC45.10, IC46.4, IC48.10
/MEMWR: IC46.6, IC47.10
/MRST: C57.2, IC27.12, IC49.1, R16.1
/NADDR11: IC19.5, IC20.10
/NBOTH: IC48.4, IC48.12
/NGFX: IC32.13, IC45.12, IC46.2
/NMUX: IC19.11, IC35.1, IC36.1, IC37.1, IC38.1, IC45.2, IC54.1
/NVSYNC: IC46.12, JP4.3
/OEY: IC1.5, IC54.3
/OSCIN: IC20.1, Q2.1, R8.1
/OSCMID: IC20.2, IC20.3, R8.2, R9.1
/OSCOUT: IC20.4, IC20.5, Q2.2, R9.2
/PDOE: IC32.3, IC47.12, IC50.1
/PLANE0: IC33.2, IC37.13
/PLANE1: IC33.5, IC38.3
/PLANE2: IC33.6, IC38.6
/PS2VCC: F1.2, J2.4, J3.4
/PSEL_A: IC1.1, IC30.13
/PSEL_B: IC1.2, IC30.12
/PSEL_C: IC30.11, IC31.1, IC31.4
/PSEL_D: IC30.10, IC31.9, IC31.12
/PSEL_E: IC30.9, IC32.1
/PSTOE: IC31.11, IC52.1, IC52.19
/PWRLED: LED1.2, R2.1
/QCR: IC19.12, IC32.8
/RCO: IC19.9, IC19.10, IC28.15, IC32.10
/RDCMD: IC49.13, IC51.1, IC53.13, R23.1
/RESETB: IC27.11, IC54.8
/RESETH: IC27.10, IC27.13, R21.1
/SEL0: IC18.10, RN2.2, SV3.7
/SEL1: IC18.12, RN2.3, SV3.5
/SEL2: IC18.13, RN2.4, SV3.3
/SEL3: IC18.15, RN2.5, SV3.1
/SRC: IC49.19, IC52.4
/SRDOE: IC41.1, IC48.8
/STATOE: IC31.6, IC34.1, IC34.19
/SYNC: IC27.4, IC27.6, J1.C1, R11.1, R12.2
/TD: IC1.9, IC26.6
/TDG: IC1.8, IC32.4, IC48.1
/TDOT: IC24.13, IC26.5
/TEXTOFF: IC33.15, IC46.9
/TEXTON: IC1.10, IC46.8
/TXTCE: IC15.47, IC19.6
/TXTONLY: IC34.8, IC44.9, R27.1
/VADDR0: IC15.6, IC17.4, IC35.2
/VADDR1: IC15.7, IC17.5, IC35.5
/VADDR2: IC15.8, IC17.6, IC35.11
/VADDR3: IC15.9, IC17.7, IC35.14
/VADDR4: IC15.10, IC17.8, IC36.2
/VADDR5: IC15.11, IC17.9, IC36.5
/VADDR6: IC15.12, IC17.10, IC36.11
/VADDR7: IC15.13, IC17.11, IC36.14
/VADDR8: IC15.14, IC17.12, IC37.2
/VADDR9: IC15.15, IC17.13, IC37.5
/VADDR10: IC15.4, IC17.14, IC37.11
/VADDR11: IC15.3, IC17.15
/VDATA0: IC15.16, IC23.14
/VDATA1: IC15.17, IC23.13
/VDATA2: IC15.18, IC23.11
/VDATA3: IC15.19, IC23.6
/VDATA4: IC15.20, IC23.4
/VDATA5: IC15.21, IC23.3
/VDATA7: IC15.23, IC26.2
/VIDEO: IC27.2, R11.2, X2.7
/VIDN: IC27.1, IC48.6
/VMA: IC18.3, IC20.12
/VROWS0: IC17.38, IC25.10, IC37.14
/VROWS1: IC17.37, IC25.9, IC38.2
/VROWS2: IC17.36, IC25.8, IC38.5
/VSBUF: IC46.13, IC54.11, JP4.1
/VSYNC: IC17.40, IC27.3, IC34.4, IC54.12, IC54.13
/WEPH: IC26.11, IC32.12
/WEPH2: IC32.11, IC45.4
/WRQ: IC1.4, IC44.5, IC45.1, R26.1
/WSLOT: IC1.6, IC39.22
/XORM: IC33.19, IC48.13
/XT1: C55.1, IC49.9, Y1.1
/XT2: C56.1, IC49.10, Y1.2
/XTAL: IC20.6, IC21.14, SV4.1
/XTALDIV2: IC20.9, IC21.1, IC21.12
GND: C3.2, C16.2, C17.2, C18.2, C19.2, C20.2, C21.2, C22.2, C23.2, C24.2, C25.2, C26.2, C27.2, C28.2, C29.2, C30.2, C31.2, C32.2, C33.2, C34.2, C35.2, C36.2, C37.2, C38.2, C39.2, C40.2, C41.2, C42.2, C43.2, C44.2, C45.2, C46.2, C47.2, C48.2, C49.2, C50.2, C51.2, C52.2, C53.2, C54.2, C55.2, C56.2, C58.2, C59.2, IC1.7, IC15.1, IC15.5, IC15.24, IC15.45, IC17.1, IC17.3, IC18.2, IC18.4, IC18.8, IC19.7, IC20.7, IC21.2, IC21.3, IC21.6, IC21.7, IC21.10, IC22.8, IC23.8, IC24.1, IC24.6, IC24.8, IC25.2, IC25.14, IC25.20, IC25.22, IC25.23, IC25.24, IC26.7, IC27.7, IC28.3, IC28.5, IC28.8, IC30.4, IC30.5, IC30.8, IC31.7, IC32.7, IC33.10, IC34.10, IC34.13, IC34.17, IC35.8, IC35.15, IC36.8, IC36.15, IC37.8, IC37.15, IC38.8, IC38.13, IC38.14, IC38.15, IC39.14, IC39.20, IC40.10, IC41.10, IC42.1, IC42.10, IC43.1, IC43.6, IC43.8, IC44.7, IC44.11, IC44.12, IC44.13, IC45.7, IC46.7, IC47.7, IC48.7, IC49.8, IC49.22, IC50.10, IC51.10, IC52.8, IC52.10, IC52.11, IC52.13, IC52.15, IC52.17, IC53.7, IC54.7, IC55.10, J1.S1, J1.S2, J1.S3, J2.3, J2.S, J3.3, J3.S, J4.1, J4.2, JP2.2, LED1.1, R24.2, R25.2, R26.2, SV3.2, SV3.4, SV3.6, SV3.8, X1.A1, X1.A32, X1.B1, X1.B32, X1.C1, X1.C32, X2.1, X2.2, X2.G1, X2.G2
VCC: C3.1, C16.1, C17.1, C18.1, C19.1, C20.1, C21.1, C22.1, C23.1, C24.1, C25.1, C26.1, C27.1, C28.1, C29.1, C30.1, C31.1, C32.1, C33.1, C34.1, C35.1, C36.1, C37.1, C38.1, C39.1, C40.1, C41.1, C42.1, C43.1, C44.1, C45.1, C46.1, C47.1, C48.1, C49.1, C50.1, C51.1, C52.1, C53.1, C54.1, C58.1, C59.1, F1.1, IC1.14, IC15.2, IC15.48, IC17.20, IC18.16, IC19.14, IC20.14, IC21.5, IC22.16, IC23.16, IC24.16, IC25.27, IC25.28, IC26.14, IC27.14, IC28.1, IC28.6, IC28.16, IC30.16, IC31.14, IC32.14, IC33.20, IC34.11, IC34.15, IC34.20, IC35.16, IC36.16, IC37.16, IC38.16, IC39.28, IC40.20, IC41.20, IC42.20, IC43.16, IC44.10, IC44.14, IC45.13, IC45.14, IC46.14, IC47.14, IC48.14, IC49.7, IC49.20, IC50.20, IC51.20, IC52.20, IC53.2, IC53.4, IC53.10, IC53.12, IC53.14, IC54.10, IC54.14, IC55.20, R2.2, R10.2, R12.1, R15.1, R16.2, R17.2, R18.2, R19.2, R20.2, R21.2, R22.2, R23.2, R27.2, RN2.1, RN3.1, X1.A2, X1.A31, X1.B2, X1.B31, X1.C2, X1.C31

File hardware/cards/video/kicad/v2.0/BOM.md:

# Video card V2.0 - bill of materials

GENERATED by `gen_v20.py bom` from `v20_netlist.py` (2026-10-26) - do not edit. 121 parts. Buy every IC in a socket (the 6845, the IDT7134, the 28C64, the 62256 and the ATmega at least); the placement leaves room for stamped sockets with end walls up to 1.9 mm (R2-2, `gen_v20.py place`). **Text-only build** (the recommended first build, README): leave off the parts marked *off*, fit the ones marked *only*.

| Qty | Value | Footprint | References | Text-only | Buy / note |
|---|---|---|---|---|---|
| 30 | 100n | C_Disc_D5.0mm_W2.5mm_P2.50mm | C3, C17, C18, C19, C20, C21, C22, C23, C24, C25, C26, C27, C28, C29, C30, C31, C32, C33, C34, C46, C47, C48, C49, C50, C51, C52, C53, C54, C57, C58 |  | ceramic X7R, 50 V, 2.5 mm lead spacing |
| 1 | 47u 16V | CP_Radial_D6.3mm_P2.50mm | C16 |  | 47 uF electrolytic, 16 V or more, radial 6.3 mm, 2.5 mm pitch (R2-7) |
| 12 | 100n | C_Disc_D5.0mm_W2.5mm_P2.50mm | C35, C36, C37, C38, C39, C40, C41, C42, C43, C44, C45, C59 | off | ceramic X7R, 50 V, 2.5 mm lead spacing |
| 2 | 22p | C_Disc_D5.0mm_W2.5mm_P2.50mm | C55, C56 |  | ceramic C0G (NP0), 50 V, 2.5 mm lead spacing |
| 1 | 0.5A PTC | Fuse_Bourns_MF-RHT050 | F1 |  | Bourns MF-RHT050 (0.5 A hold, radial) |
| 1 | 74ALS08 | DIP-14_W7.62mm | IC1 |  |  |
| 1 | IDT7134 | DIP-48_W15.24mm | IC15 |  | IDT7134 (SA/LA, 55-90 ns, DIP-48), or the V1.0 card's chip |
| 1 | HD68B45SP / MC68B45P | DIP-40_W15.24mm | IC17 |  | HD68B45SP (Hitachi) or MC68B45P (Motorola), the 2 MHz (B) bus grade: a 6 MHz CPU's OUT gives E 333 ns high (PWEH 220 ns in the B grade, 450 in the 1 MHz grade) and 6-dot mode needs its clock-low time (V2-11, R2-7). HD6845SP / MC6845P (the 1 MHz grades) only with a 1 MHz CPU and the V2-11 clock-low check in 6-dot mode. Hitachi's letters (HD6845S / HD68A45S / HD68B45S = 1.0 / 1.5 / 2.0 MHz) to verify on the part's data sheet |
| 1 | 74S85 | DIP-16_W7.62mm | IC18 |  | 74S85 (the V1.x card's; a 74LS85 also works: see the README) |
| 1 | 74LS00 | DIP-14_W7.62mm | IC19 |  | 74LS00; a 74ALS00 adds a little more CHARCLOCK margin (R3-1) |
| 2 | 74LS04 | DIP-14_W7.62mm | IC20, IC46 |  |  |
| 1 | 74LS90 | DIP-14_W7.62mm | IC21 |  |  |
| 1 | 74LS175 | DIP-16_W7.62mm | IC22 |  |  |
| 1 | 74LS174 | DIP-16_W7.62mm | IC23 |  |  |
| 1 | 74LS166 | DIP-16_W7.62mm | IC24 |  |  |
| 1 | AT28C64B-15 | DIP-28_W15.24mm | IC25 |  | AT28C64B-15PU (Microchip), 150 ns, burned with chargen-v20.bin (minipro -p AT28C64B -u -P -w) |
| 1 | 74LS86 | DIP-14_W7.62mm | IC26 |  |  |
| 1 | 7416 | DIP-14_W7.62mm | IC27 |  |  |
| 1 | 74LS163 | DIP-16_W7.62mm | IC28 |  | 74F163A or 74ALS163B (same pinout; R3-1: with a 74LS163, CHARCLOCK's set-up to the 74LS166s' SH/-LD is ~3 ns at worst-case delays, ~24 ns typical); keep a spare 74F163 |
| 1 | 74LS138 | DIP-16_W7.62mm | IC30 |  |  |
| 2 | 74LS32 | DIP-14_W7.62mm | IC31, IC32 |  |  |
| 1 | 74HCT273 | DIP-20_W7.62mm | IC33 |  |  |
| 2 | 74LS244 | DIP-20_W7.62mm | IC34, IC52 |  |  |
| 4 | 74LS157 | DIP-16_W7.62mm | IC35, IC36, IC37, IC38 | off |  |
| 1 | 62256 | DIP-28_W15.24mm | IC39 | off | AS6C62256-55PCN (Alliance, 55 ns, 600-mil DIP-28): -55 recommended (current production); a slower 62256 works in direct mode up to the machine's 6 MHz and in slot mode in 8-dot mode (R2-8); not a 300-mil 'skinny' 62256 |
| 1 | 74HCT244 | DIP-20_W7.62mm | IC40 | off |  |
| 1 | 74HCT374 | DIP-20_W7.62mm | IC41 | off | 74HCT374; a 74ACT374 (24 mA) if DATA0's low level during a window read is above 0.5 V (R2-6) |
| 1 | 74LS374 | DIP-20_W7.62mm | IC42 | off |  |
| 1 | 74LS166 | DIP-16_W7.62mm | IC43 | off |  |
| 1 | 74LS74 | DIP-14_W7.62mm | IC44 | off |  |
| 1 | 74LS20 | DIP-14_W7.62mm | IC45 | off |  |
| 1 | 74LS08 | DIP-14_W7.62mm | IC47 |  |  |
| 1 | 74LS10 | DIP-14_W7.62mm | IC48 |  |  |
| 1 | ATmega328P-P | DIP-28_W7.62mm | IC49 |  | ATmega328P-PU with the Arduino Uno bootloader burned (ISP) before fitting |
| 1 | 74LS374 | DIP-20_W7.62mm | IC50 |  |  |
| 1 | 74HCT374 | DIP-20_W7.62mm | IC51 |  |  |
| 1 | 74HCT74 | DIP-14_W7.62mm | IC53 |  |  |
| 1 | 74HCT08 | DIP-14_W7.62mm | IC54 |  |  |
| 1 | 74HCT244 | DIP-20_W7.62mm | IC55 | off | 74HCT244; a 74ACT244 (24 mA) if DATA0's low level during a window read is above 0.5 V (R2-6) |
| 1 | RCA | RCA | J1 |  | RCA jack, right-angle PCB mount: the V1.0 card's part (the footprint is V1.0's) |
| 1 | KEYBOARD | MiniDIN6_MD-60SM | J2 |  | Same Sky (CUI Devices) MD-60SM, date code after 2022-03-03 (the footprint follows that layout) |
| 1 | MOUSE | MiniDIN6_MD-60SM | J3 |  | Same Sky (CUI Devices) MD-60SM, date code after 2022-03-03 |
| 1 | FTDI | PinHeader_1x06_P2.54mm_Vertical | J4 |  | 1x6 pin header; a 5 V FTDI cable (TTL-232R-5V) or a 5 V FTDI Basic |
| 1 | DOTS 8=ON | PinHeader_1x02_P2.54mm_Vertical | JP2 |  |  |
| 1 | INT-EN | PinHeader_1x02_P2.54mm_Vertical | JP3 |  |  |
| 1 | VSYNC +/- | PinHeader_1x03_P2.54mm_Vertical | JP4 |  | 1x3 pin header and a shunt: 1-2 (+VSYNC) for a TV-rate or CGA monitor, 2-3 (-VSYNC) for an MDA monitor |
| 1 | PWR | LED_D5.0mm | LED1 |  |  |
| 1 | 12MHz | Crystal_HC49-U_Vertical | Q2 |  | 12 MHz, HC-49/U |
| 1 | 330 | R_Axial_DIN0207_L6.3mm_D2.5mm_P10.16mm_Horizontal | R2 |  |  |
| 3 | 1k | R_Axial_DIN0207_L6.3mm_D2.5mm_P7.62mm_Horizontal | R8, R9, R10 |  |  |
| 1 | 33 | R_Axial_DIN0207_L6.3mm_D2.5mm_P7.62mm_Horizontal | R11 |  |  |
| 1 | 270 | R_Axial_DIN0207_L6.3mm_D2.5mm_P7.62mm_Horizontal | R12 |  |  |
| 6 | 4.7k | R_Axial_DIN0207_L6.3mm_D2.5mm_P7.62mm_Horizontal | R15, R17, R18, R19, R20, R21 |  |  |
| 5 | 10k | R_Axial_DIN0207_L6.3mm_D2.5mm_P7.62mm_Horizontal | R16, R22, R23, R24, R27 |  |  |
| 2 | 1k | R_Axial_DIN0207_L6.3mm_D2.5mm_P7.62mm_Horizontal | R25, R26 | only |  |
| 1 | 10k x4 | R_Array_SIP5 | RN2 |  | 10k x4 BUSSED, pin 1 common, 5-pin SIP (e.g. Bourns 4605X-101-103LF); not an isolated network, which would leave SEL0-3 without pull-ups (R3-15) |
| 1 | 10k x8 | R_Array_SIP9 | RN3 | off | 10k x8 BUSSED, pin 1 common, 9-pin SIP (e.g. Bourns 4609X-101-103LF); not an isolated network, which would leave GD0-7 without pull-ups (R3-15) |
| 1 | BLOCK | PinHeader_2x04_P2.54mm_Vertical | SV3 |  |  |
| 1 | DOTCLK | PinHeader_1x03_P2.54mm_Vertical | SV4 |  |  |
| 1 | DIN41612 96 | FABC96R | X1 |  |  |
| 1 | DB9 F | F09HP | X2 |  | DE-9 female, right-angle PCB mount: the V1.0 card's part, or check a new one's pin pitch first - the F09HP footprint is 2.74 mm pitch, 2.54 mm between rows (most DE-9s 2.77 / 2.84 mm; R3-16) |
| 1 | 16MHz | Crystal_HC49-U_Vertical | Y1 |  | 16 MHz, HC-49/U, parallel resonant, 18-20 pF load (for C55 / C56 22 pF, as on an Arduino Uno) |

Fitted in both builds: everything not marked *off* or *only*. The text-only build leaves off 25 parts (IC35, IC36, IC37, IC38, IC39, IC40, IC41, IC42, IC43, IC44, IC45, IC55, RN3, C35, C36, C37, C38, C39, C40, C41, C42, C43, C44, C45, C59) and fits R25, R26.
